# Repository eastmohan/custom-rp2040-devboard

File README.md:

**RP2040 Devboard** </br>
A custom devboard using the RP2040 chip. I made this to get a better understanding of how devboards work. I also wanted to get better at PCB design, which this definitely helped with thanks to the high amount of traces to route in a small footprint.

**BOM** </br>
| Part | Link | Price | 
| ------- | ------- | -------- |
| Custom PCBA | [Link](https://cart.jlcpcb.com/quote/gerberviewThree/?qs=693d5b279bb64dad9bc01a3e98fce2fa_1_0_1_0_0.html) | $44.69 |

</br>

All footprints and symbols used should be in KiCAD by default (KiCAD 10.0 or later).

**Images**

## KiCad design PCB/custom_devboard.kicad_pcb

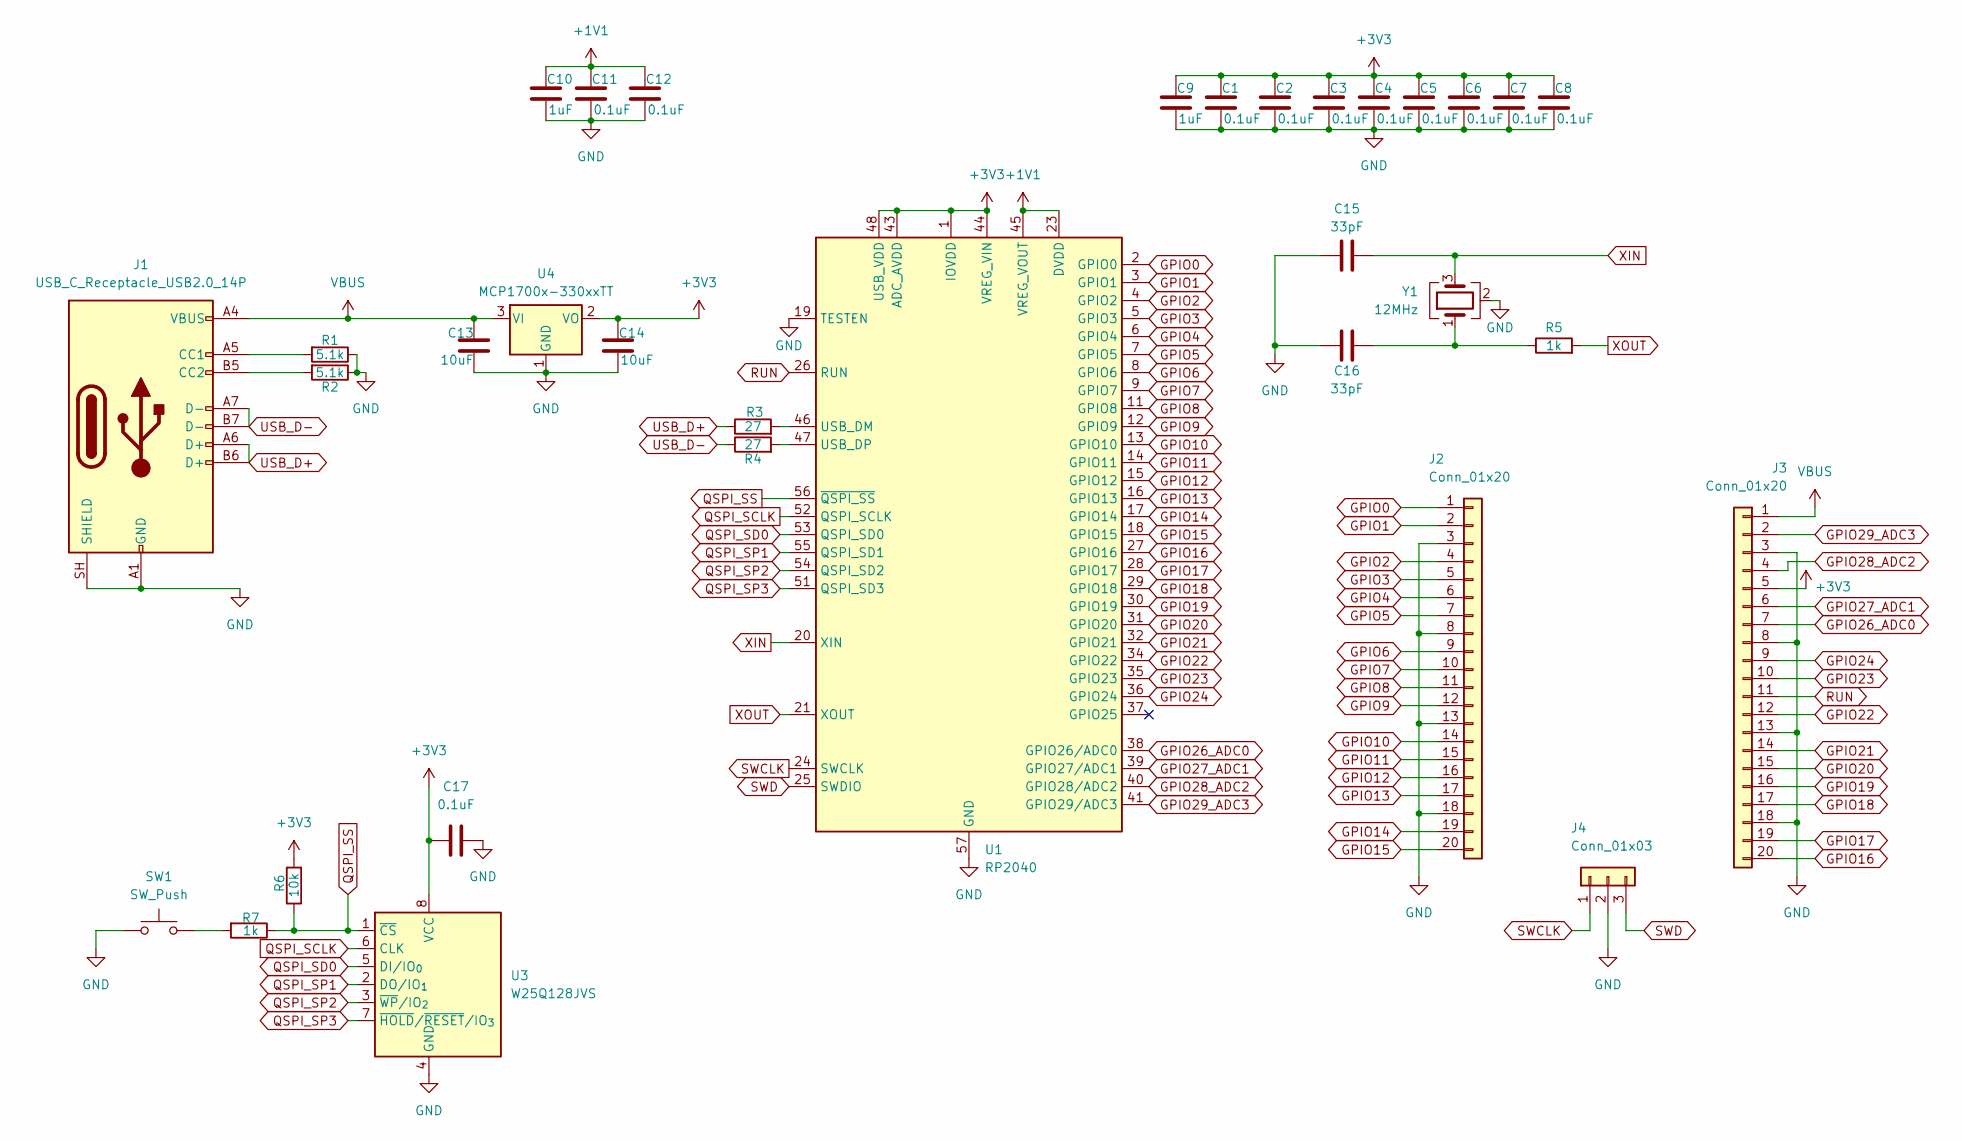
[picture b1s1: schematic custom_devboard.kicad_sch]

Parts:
C1, C2, C3, C4, C5, C6, C7, C8, C11, C12, C17: 0.1uF; C_0402_1005Metric
C9, C10: 1uF; C_0402_1005Metric
C13, C14: 10uF; C_0603_1608Metric
C15, C16: 33pF; C_0402_1005Metric
J1: USB_C_Receptacle_USB2.0_14P; USB_C_Receptacle_HRO_TYPE-C-31-M-12
J2, J3: Conn_01x20; PinHeader_1x20_P2.54mm_Vertical
J4: Conn_01x03; PinHeader_1x03_P2.54mm_Vertical
R1, R2: 5.1k; R_0402_1005Metric
R3, R4: 27; R_0402_1005Metric
R5, R7: 1k; R_0402_1005Metric
R6: 10k; R_0402_1005Metric
SW1: SW_Push; SW_Push_SPST_NO_Alps_SKRK
U1: RP2040; QFN-56-1EP_7x7mm_P0.4mm_EP3.2x3.2mm
U3: W25Q128JVS; SOIC-8_5.3x5.3mm_P1.27mm
U4: MCP1700x-330xxTT; SOT-23
Y1: 12MHz; Crystal_SMD_3225-4Pin_3.2x2.5mm

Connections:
+1V1: C10.1, C11.1, C12.1, U1.23 (DVDD), U1.45 (VREG_VOUT), U1.50 (DVDD)
+3V3: C1.1, C2.1, C3.1, C4.1, C5.1, C6.1, C7.1, C8.1, C9.1, C14.1, C17.1, J3.5, R6.2, U1.1 (IOVDD), U1.10 (IOVDD), U1.22 (IOVDD), U1.33 (IOVDD), U1.42 (IOVDD), U1.43 (ADC_AVDD), U1.44 (VREG_VIN), U1.48 (USB_VDD), U1.49 (IOVDD), U3.8 (VCC), U4.2 (VO)
GND: C1.2, C2.2, C3.2, C4.2, C5.2, C6.2, C7.2, C8.2, C9.2, C10.2, C11.2, C12.2, C13.2, C14.2, C15.1, C16.1, C17.2, J1.A1 (GND), J1.A12 (GND), J1.B1 (GND), J1.B12 (GND), J1.SH (SHIELD), J2.3, J2.8, J2.13, J2.18, J3.3, J3.8, J3.13, J3.18, J4.2, R1.1, R2.1, SW1.1, U1.19 (TESTEN), U1.57 (GND), U3.4 (GND), U4.1 (GND), Y1.2 (G), Y1.4 (G)
GPIO0: J2.1, U1.2 (GPIO0)
GPIO1: J2.2, U1.3 (GPIO1)
GPIO2: J2.4, U1.4 (GPIO2)
GPIO3: J2.5, U1.5 (GPIO3)
GPIO4: J2.6, U1.6 (GPIO4)
GPIO5: J2.7, U1.7 (GPIO5)
GPIO6: J2.9, U1.8 (GPIO6)
GPIO7: J2.10, U1.9 (GPIO7)
GPIO8: J2.11, U1.11 (GPIO8)
GPIO9: J2.12, U1.12 (GPIO9)
GPIO10: J2.14, U1.13 (GPIO10)
GPIO11: J2.15, U1.14 (GPIO11)
GPIO12: J2.16, U1.15 (GPIO12)
GPIO13: J2.17, U1.16 (GPIO13)
GPIO14: J2.19, U1.17 (GPIO14)
GPIO15: J2.20, U1.18 (GPIO15)
GPIO16: J3.20, U1.27 (GPIO16)
GPIO17: J3.19, U1.28 (GPIO17)
GPIO18: J3.17, U1.29 (GPIO18)
GPIO19: J3.16, U1.30 (GPIO19)
GPIO20: J3.15, U1.31 (GPIO20)
GPIO21: J3.14, U1.32 (GPIO21)
GPIO22: J3.12, U1.34 (GPIO22)
GPIO23: J3.10, U1.35 (GPIO23)
GPIO24: J3.9, U1.36 (GPIO24)
GPIO26_ADC0: J3.7, U1.38 (GPIO26/ADC0)
GPIO27_ADC1: J3.6, U1.39 (GPIO27/ADC1)
GPIO28_ADC2: J3.4, U1.40 (GPIO28/ADC2)
GPIO29_ADC3: J3.2, U1.41 (GPIO29/ADC3)
unnamed: C16.2, R5.1, Y1.1
unnamed: J1.A5 (CC1), R1.2
unnamed: J1.B5 (CC2), R2.2
unnamed: R7.2, SW1.2
unnamed: R3.2, U1.46 (USB_DM)
unnamed: R4.2, U1.47 (USB_DP)
QSPI_SCLK: U1.52 (QSPI_SCLK), U3.6 (CLK)
QSPI_SD0: U1.53 (QSPI_SD0), U3.5 (DI/IO_{0})
QSPI_SP1: U1.55 (QSPI_SD1), U3.2 (DO/IO_{1})
QSPI_SP2: U1.54 (QSPI_SD2), U3.3 (~WP/IO_{2})
QSPI_SP3: U1.51 (QSPI_SD3), U3.7 (~HOLD/~RESET/IO_{3})
QSPI_SS: R6.1, R7.1, U1.56 (~QSPI_SS), U3.1 (~CS)
RUN: J3.11, U1.26 (RUN)
SWCLK: J4.1, U1.24 (SWCLK)
SWD: J4.3, U1.25 (SWDIO)
USB_D+: J1.A6 (D+), J1.B6 (D+), R3.1
USB_D-: J1.A7 (D-), J1.B7 (D-), R4.1
VBUS: C13.1, J1.A4 (VBUS), J1.A9 (VBUS), J1.B4 (VBUS), J1.B9 (VBUS), J3.1, U4.3 (VI)
XIN: C15.2, U1.20 (XIN), Y1.3
XOUT: R5.2, U1.21 (XOUT)

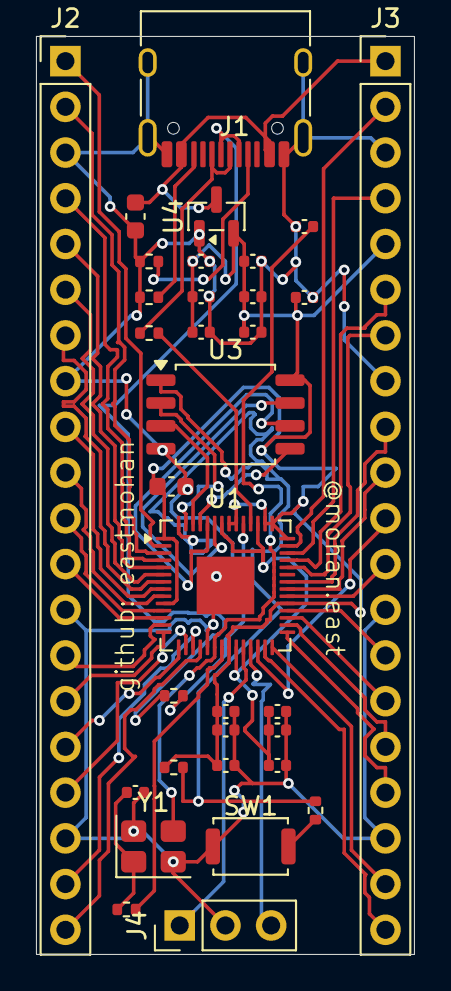
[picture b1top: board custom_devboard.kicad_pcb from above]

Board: 2 copper layers, 21.0 x 51.0 mm, 33 parts (0 on the bottom side), 52 nets.

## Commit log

2026-05-04 Added PCB Files
2026-05-04 Added CAD
